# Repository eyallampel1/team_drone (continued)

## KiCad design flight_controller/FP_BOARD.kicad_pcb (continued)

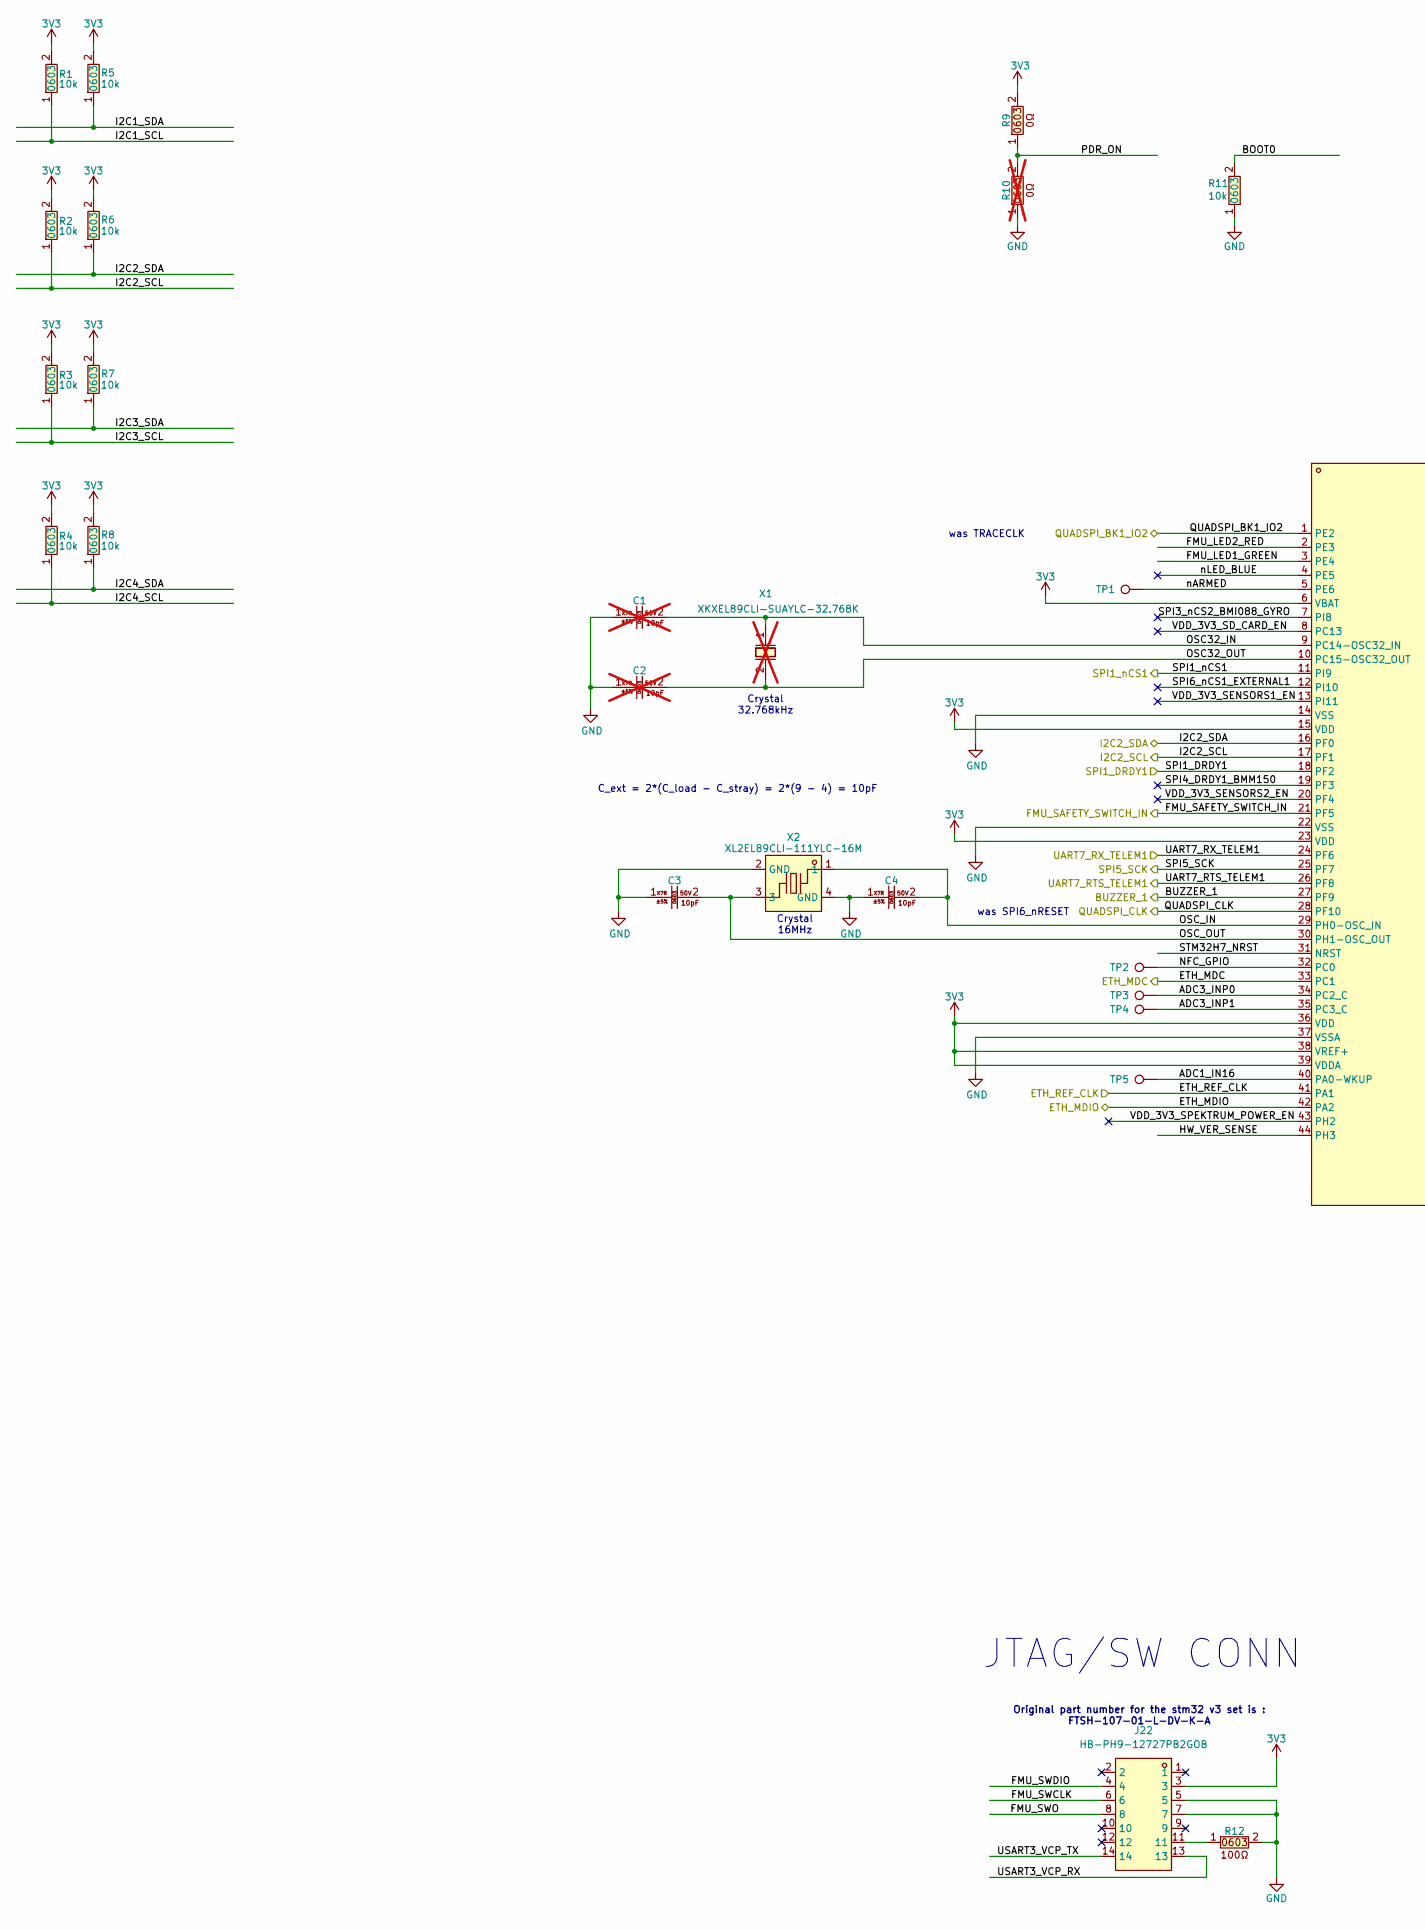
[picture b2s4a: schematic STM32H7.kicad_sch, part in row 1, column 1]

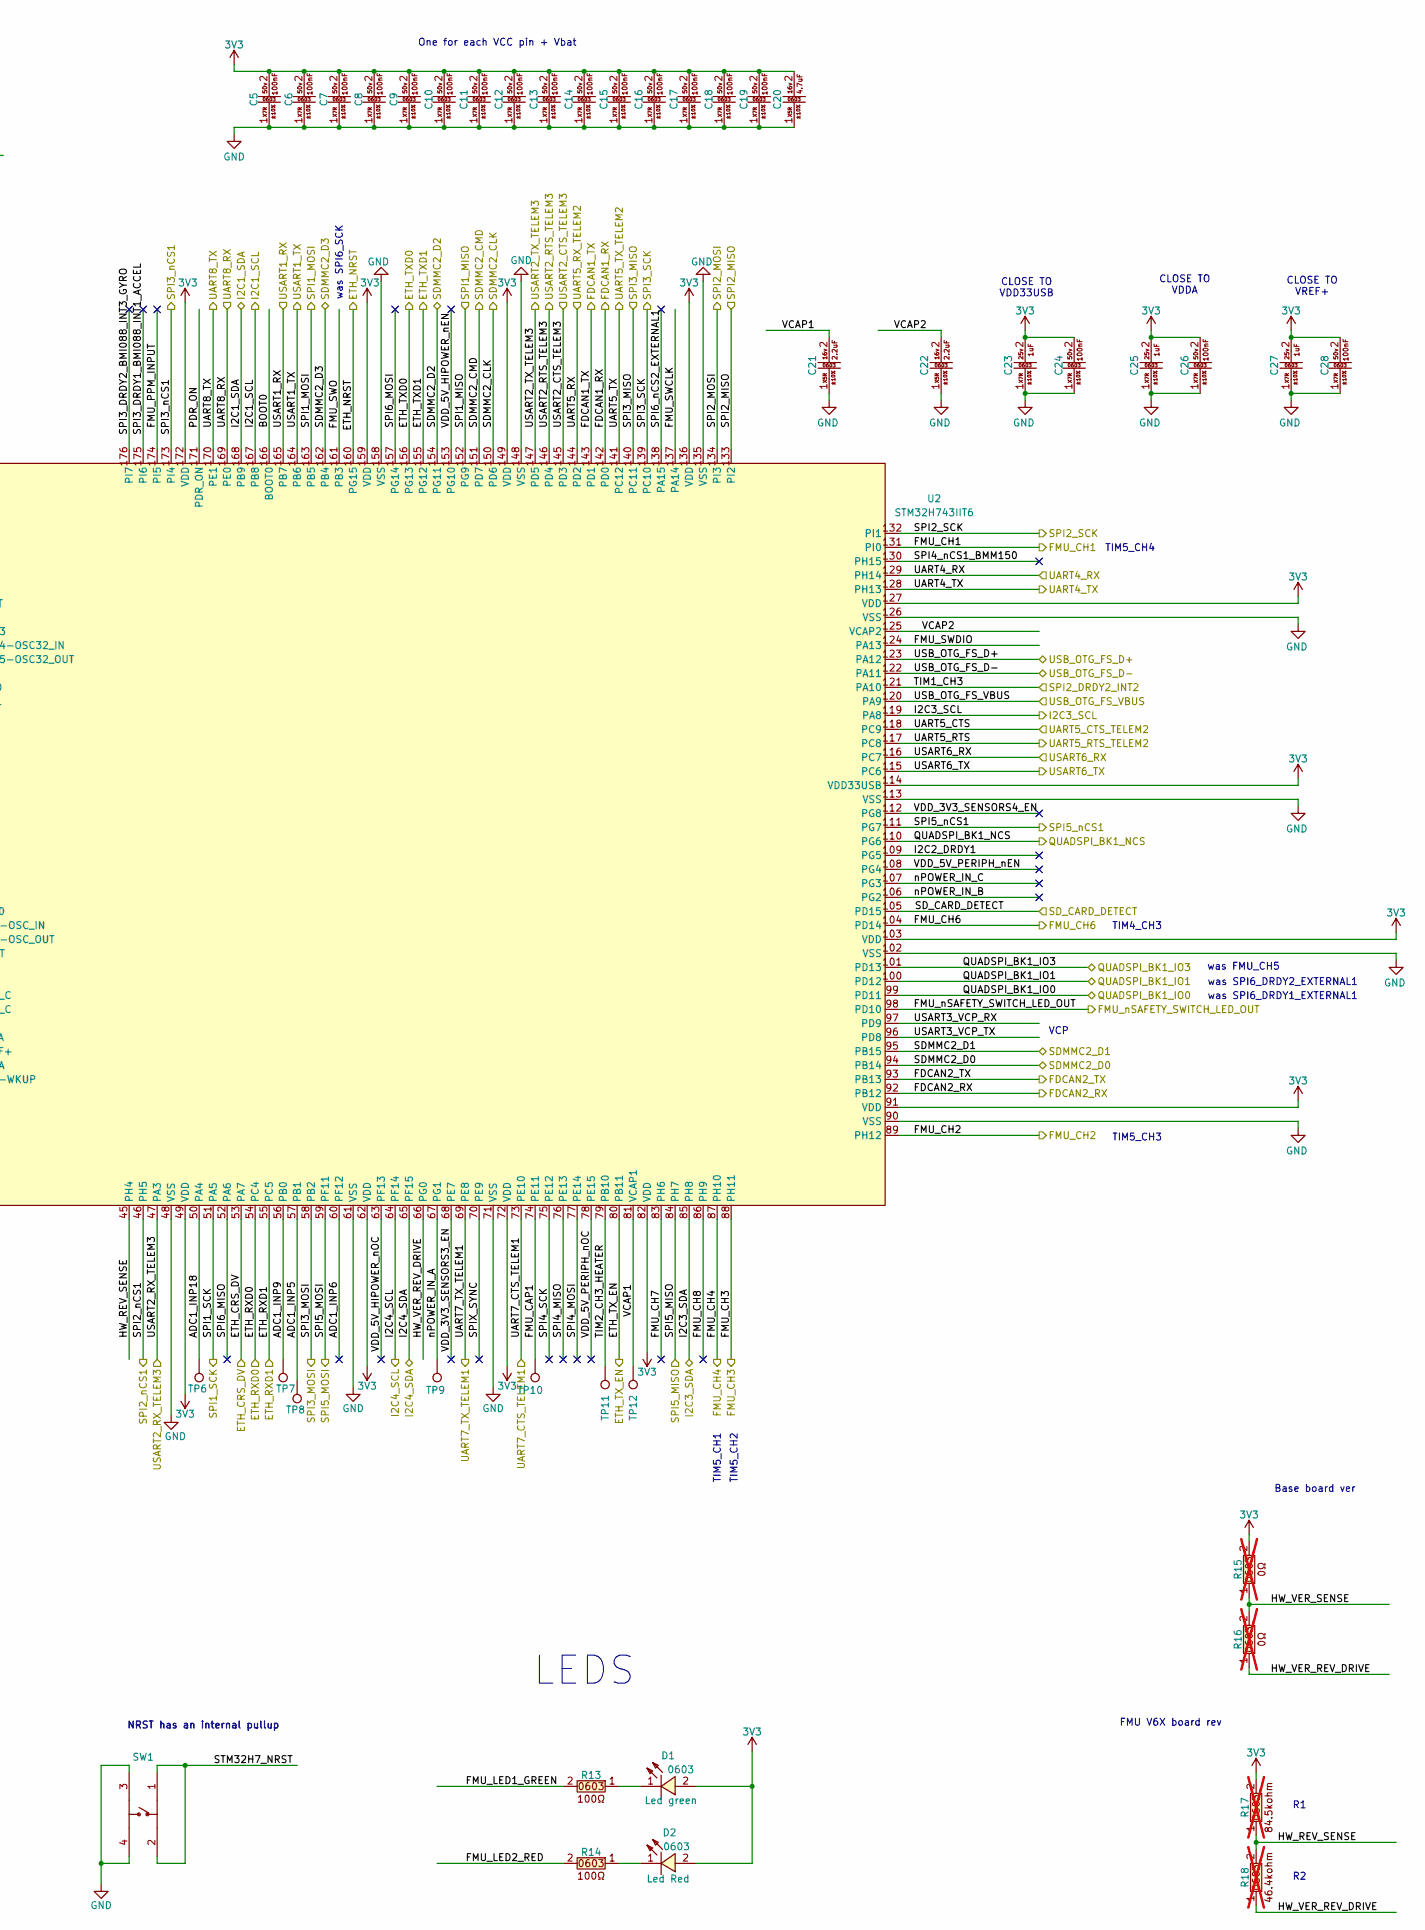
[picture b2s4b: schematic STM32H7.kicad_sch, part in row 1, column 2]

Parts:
C1, C2: CC0603JRNPO9BN100 (10pF , 0603 ,50V ,X7R); C0603; LCSC Part C106245; not fitted
C3, C4: CC0603JRNPO9BN100 (10pF , 0603 ,50V ,X7R); C0603; LCSC Part C106245
C5, C6, C7, C8, C9, C10, C11, C12, C13, C14, C15, C16, C17, C18, C19, C24, C26, C28: CC0603KRX7R9BB104 (100nf , 0603 ,50v ,X7R); C0603; LCSC Part C14663
C20: CL10A475KO8NNNC (4.7uf , 0603 ,16v ,X5R); C0603; LCSC Part C19666
C21, C22: CL10A225KO8NNNC (2.2uf , 0603,16v,X5R); C0603; LCSC Part C23630
C23, C25, C27: CL10B105KA8NNNC (1uf ,0603 ,25v ,X7R); C0603; LCSC Part C29936
D1: 0603 Green 509-620mcd; LED0603-RD; LCSC Part C12624
D2: KT-0603R; LED0603-RD; LCSC Part C2286
J22: HB-PH9-12727PB2GOB; HDR-SMD_14P-P1.27-V-M-R2-C7-LS5.5; LCSC Part C6332251
R1, R2, R3, R4, R5, R6, R7, R8, R11: 0603WAF1002T5E; R0603; LCSC Part C25804
R9: 603WAF0000T5E (0ohm , 0603); R0603; LCSC Part C21189
R10, R15, R16: 603WAF0000T5E (0ohm , 0603); R0603; LCSC Part C21189; not fitted
R12, R13, R14: 603WAF1000T5E (100ohm , 0603); R0603; LCSC Part C22775
R17: 0603WAF8452T5E (84.5kohm , 0603); R0603; LCSC Part C23118; not fitted
R18: FRC0603F4642TS (46.4kohm , 0603); R0603; LCSC Part C3013203; not fitted
SW1: 6.0*6.0*6.0; SW-SMD_4P-L6.0-W6.0-P4.50-LS8.6; LCSC Part C5127964
TP1, TP2, TP3, TP4, TP5, TP6, TP7, TP8, TP9, TP10, TP11, TP12: TestPoint; TestPoint_Pad_2.0x2.0mm
U2: STM32H743IIT6; LQFP-176_L24.0-W24.0-P0.50-LS26.0-BL; LCSC Part C89597
X1: XKXEL89CLI-SUAYLC-32.768K; OSC-SMD_2P-L3.2-W1.5; LCSC Part C17179430; not fitted
X2: XL2EL89CLI-111YLC-16M; CRYSTAL-SMD_4P-L3.2-W2.5-BL; LCSC Part C5444547

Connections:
/BUZZER_1: U2.27 (PF9); also elsewhere on the board
/ETH_CRS_DV: U2.53 (PA7); also elsewhere on the board
/ETH_MDC: U2.33 (PC1); also elsewhere on the board
/ETH_MDIO: U2.42 (PA2); also elsewhere on the board
/ETH_NRST: U2.160 (PG15); also elsewhere on the board
/ETH_REF_CLK: U2.41 (PA1); also elsewhere on the board
/ETH_RXD0: U2.54 (PC4); also elsewhere on the board
/ETH_RXD1: U2.55 (PC5); also elsewhere on the board
/ETH_TXD0: U2.156 (PG13); also elsewhere on the board
/ETH_TXD1: U2.155 (PG12); also elsewhere on the board
/ETH_TX_EN: U2.80 (PB11); also elsewhere on the board
/FDCAN1_RX: U2.142 (PD0); also elsewhere on the board
/FDCAN1_TX: U2.143 (PD1); also elsewhere on the board
/FDCAN2_RX: U2.92 (PB12); also elsewhere on the board
/FDCAN2_TX: U2.93 (PB13); also elsewhere on the board
/FMU_CH1: U2.131 (PI0); also elsewhere on the board
/FMU_CH2: U2.89 (PH12); also elsewhere on the board
/FMU_CH3: U2.88 (PH11); also elsewhere on the board
/FMU_CH4: U2.87 (PH10); also elsewhere on the board
/FMU_CH6: U2.104 (PD14); also elsewhere on the board
/FMU_SAFETY_SWITCH_IN: U2.21 (PF5); also elsewhere on the board
/FMU_nSAFETY_SWITCH_LED_OUT: U2.98 (PD10); also elsewhere on the board
/I2C1_SCL: R1.1, U2.167 (PB8); also elsewhere on the board
/I2C1_SDA: R5.1, U2.168 (PB9); also elsewhere on the board
/I2C2_SCL: R2.1, U2.17 (PF1); also elsewhere on the board
/I2C2_SDA: R6.1, U2.16 (PF0); also elsewhere on the board
/I2C3_SCL: R3.1, U2.119 (PA8); also elsewhere on the board
/I2C3_SDA: R7.1, U2.85 (PH8); also elsewhere on the board
/I2C4_SCL: R4.1, U2.64 (PF14); also elsewhere on the board
/I2C4_SDA: R8.1, U2.65 (PF15); also elsewhere on the board
/QUADSPI_BK1_IO0: U2.99 (PD11); also elsewhere on the board
/QUADSPI_BK1_IO1: U2.100 (PD12); also elsewhere on the board
/QUADSPI_BK1_IO2: U2.1 (PE2); also elsewhere on the board
/QUADSPI_BK1_IO3: U2.101 (PD13); also elsewhere on the board
/QUADSPI_BK1_NCS: U2.110 (PG6); also elsewhere on the board
/QUADSPI_CLK: U2.28 (PF10); also elsewhere on the board
/SDMMC2_CLK: U2.150 (PD6); also elsewhere on the board
/SDMMC2_CMD: U2.151 (PD7); also elsewhere on the board
/SDMMC2_D0: U2.94 (PB14); also elsewhere on the board
/SDMMC2_D1: U2.95 (PB15); also elsewhere on the board
/SDMMC2_D2: U2.154 (PG11); also elsewhere on the board
/SDMMC2_D3: U2.162 (PB4); also elsewhere on the board
/SD_CARD_DETECT: U2.105 (PD15); also elsewhere on the board
/SPI1_DRDY1: U2.18 (PF2); also elsewhere on the board
/SPI1_MISO: U2.152 (PG9); also elsewhere on the board
/SPI1_MOSI: U2.163 (PB5); also elsewhere on the board
/SPI1_SCK: U2.51 (PA5); also elsewhere on the board
/SPI1_nCS1: U2.11 (PI9); also elsewhere on the board
/SPI2_DRDY2_INT2: U2.121 (PA10); also elsewhere on the board
/SPI2_MISO: U2.133 (PI2); also elsewhere on the board
/SPI2_MOSI: U2.134 (PI3); also elsewhere on the board
/SPI2_SCK: U2.132 (PI1); also elsewhere on the board
/SPI2_nCS1: U2.46 (PH5); also elsewhere on the board
/SPI3_MISO: U2.140 (PC11); also elsewhere on the board
/SPI3_MOSI: U2.58 (PB2); also elsewhere on the board
/SPI3_SCK: U2.139 (PC10); also elsewhere on the board
/SPI3_nCS1: U2.173 (PI4); also elsewhere on the board
/SPI5_MISO: U2.84 (PH7); also elsewhere on the board
/SPI5_MOSI: U2.59 (PF11); also elsewhere on the board
/SPI5_SCK: U2.25 (PF7); also elsewhere on the board
/SPI5_nCS1: U2.111 (PG7); also elsewhere on the board
/STM32F1/USART6_RX_FROM_IO-RC_INPUT: U2.116 (PC7); also elsewhere on the board
/STM32F1/USART6_TX_TO_IO-NC: U2.115 (PC6); also elsewhere on the board
/STM32H7/ADC1_IN16: TP5.1, U2.40 (PA0-WKUP)
/STM32H7/ADC1_INP5: TP8.1, U2.57 (PB1)
/STM32H7/ADC1_INP6: U2.60 (PF12)
/STM32H7/ADC1_INP9: TP7.1, U2.56 (PB0)
/STM32H7/ADC1_INP18: TP6.1, U2.50 (PA4)
/STM32H7/ADC3_INP0: TP3.1, U2.34 (PC2_C)
/STM32H7/ADC3_INP1: TP4.1, U2.35 (PC3_C)
/STM32H7/BOOT0: R11.2, U2.166 (BOOT0)
/STM32H7/FMU_CAP1: TP10.1, U2.74 (PE11)
/STM32H7/FMU_CH7: U2.83 (PH6)
/STM32H7/FMU_CH8: U2.86 (PH9)
/STM32H7/FMU_LED1_GREEN: R13.2, U2.3 (PE4)
/STM32H7/FMU_LED2_RED: R14.2, U2.2 (PE3)
/STM32H7/FMU_PPM_INPUT: U2.174 (PI5)
/STM32H7/FMU_SWCLK: J22.6, U2.137 (PA14)
/STM32H7/FMU_SWDIO: J22.4, U2.124 (PA13)
/STM32H7/FMU_SWO: J22.8, U2.161 (PB3)
/STM32H7/HW_REV_SENSE: R17.1, R18.2, U2.45 (PH4)
/STM32H7/HW_VER_REV_DRIVE: R16.1, R18.1, U2.66 (PG0)
/STM32H7/HW_VER_SENSE: R15.1, R16.2, U2.44 (PH3)
/STM32H7/I2C2_DRDY1: U2.109 (PG5)
/STM32H7/NFC_GPIO: TP2.1, U2.32 (PC0)
/STM32H7/OSC32_IN: C1.2, U2.9 (PC14-OSC32_IN), X1.1
/STM32H7/OSC32_OUT: C2.2, U2.10 (PC15-OSC32_OUT), X1.2
/STM32H7/OSC_IN: C4.2, U2.29 (PH0-OSC_IN), X2.1
/STM32H7/OSC_OUT: C3.2, U2.30 (PH1-OSC_OUT), X2.3
/STM32H7/PDR_ON: R9.1, R10.2, U2.171 (PDR_ON)
/STM32H7/SPI3_DRDY1_BMI088_INT1_ACCEL: U2.175 (PI6)
/STM32H7/SPI3_DRDY2_BMI088_INT3_GYRO: U2.176 (PI7)
/STM32H7/SPI3_nCS2_BMI088_GYRO: U2.7 (PI8)
/STM32H7/SPI4_DRDY1_BMM150: U2.19 (PF3)
/STM32H7/SPI4_MISO: U2.76 (PE13)
/STM32H7/SPI4_MOSI: U2.77 (PE14)
/STM32H7/SPI4_SCK: U2.75 (PE12)
/STM32H7/SPI4_nCS1_BMM150: U2.130 (PH15)
/STM32H7/SPI6_MISO: U2.52 (PA6)
/STM32H7/SPI6_MOSI: U2.157 (PG14)
/STM32H7/SPI6_nCS1_EXTERNAL1: U2.12 (PI10)
/STM32H7/SPI6_nCS2_EXTERNAL1: U2.138 (PA15)
/STM32H7/SPIX_SYNC: U2.70 (PE9)
/STM32H7/STM32H7_NRST: SW1.1, SW1.2, U2.31 (NRST)
/STM32H7/TIM2_CH3_HEATER: TP11.1, U2.79 (PB10)
/STM32H7/USART3_VCP_RX: J22.13, U2.97 (PD9)
/STM32H7/USART3_VCP_TX: J22.14, U2.96 (PD8)
/STM32H7/VCAP1: C21.2, TP12.1, U2.81 (VCAP1)
/STM32H7/VCAP2: C22.2, U2.125 (VCAP2)
/STM32H7/VDD_3V3_SD_CARD_EN: U2.8 (PC13)
/STM32H7/VDD_3V3_SENSORS1_EN: U2.13 (PI11)
/STM32H7/VDD_3V3_SENSORS2_EN: U2.20 (PF4)
/STM32H7/VDD_3V3_SENSORS3_EN: U2.68 (PE7)
/STM32H7/VDD_3V3_SENSORS4_EN: U2.112 (PG8)
/STM32H7/VDD_3V3_SPEKTRUM_POWER_EN: U2.43 (PH2)
/STM32H7/VDD_5V_HIPOWER_nEN: U2.153 (PG10)
/STM32H7/VDD_5V_HIPOWER_nOC: U2.63 (PF13)
/STM32H7/VDD_5V_PERIPH_nEN: U2.108 (PG4)
/STM32H7/VDD_5V_PERIPH_nOC: U2.78 (PE15)
/STM32H7/nARMED: TP1.1, U2.5 (PE6)
/STM32H7/nLED_BLUE: U2.4 (PE5)
/STM32H7/nPOWER_IN_A: TP9.1, U2.67 (PG1)
/STM32H7/nPOWER_IN_B: U2.106 (PG2)
/STM32H7/nPOWER_IN_C: U2.107 (PG3)
/UART1_RX_GPS1: U2.165 (PB7); also elsewhere on the board
/UART1_TX_GPS1: U2.164 (PB6); also elsewhere on the board
/UART2_CTS_TELEM3: U2.145 (PD3); also elsewhere on the board
/UART2_RTS_TELEM3: U2.146 (PD4); also elsewhere on the board
/UART2_RX_TELEM3: U2.47 (PA3); also elsewhere on the board
/UART2_TX_TELEM3: U2.147 (PD5); also elsewhere on the board
/UART4_RX: U2.129 (PH14); also elsewhere on the board
/UART4_TX: U2.128 (PH13); also elsewhere on the board
/UART5_CTS_TELEM2: U2.118 (PC9); also elsewhere on the board
/UART5_RTS_TELEM2: U2.117 (PC8); also elsewhere on the board
/UART5_RX_TELEM2: U2.144 (PD2); also elsewhere on the board
/UART5_TX_TELEM2: U2.141 (PC12); also elsewhere on the board
/UART7_CTS_TELEM1: U2.73 (PE10); also elsewhere on the board
/UART7_RTS_TELEM1: U2.26 (PF8); also elsewhere on the board
/UART7_RX_TELEM1: U2.24 (PF6); also elsewhere on the board
/UART7_TX_TELEM1: U2.69 (PE8); also elsewhere on the board
/UART8_RX_GPS2: U2.169 (PE0); also elsewhere on the board
/UART8_TX_GPS2: U2.170 (PE1); also elsewhere on the board
/USB_OTG_FS_D+: U2.123 (PA12); also elsewhere on the board
/USB_OTG_FS_D-: U2.122 (PA11); also elsewhere on the board
/USB_OTG_FS_VBUS: U2.120 (PA9); also elsewhere on the board
unnamed: D1.1 (K), R13.1
unnamed: D2.1 (K), R14.1
unnamed: J22.11, R12.1

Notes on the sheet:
was SPI6_nRESET
Crystal 32.768kHz
was TRACECLK
C_ext = 2*(C_load - C_stray) = 2*(9 - 4) = 10pF
TIM4_CH3
CLOSE TO VDDA
CLOSE TO VREF+
LEDS
Original part number for the stm32 v3 set is : FTSH-107-01-L-DV-K-A
FMU V6X board rev
TIM5_CH1
NRST has an internal pullup
was FMU_CH5
Base board ver
Crystal 16MHz
TIM5_CH3
was SPI6_SCK
VCP
was SPI6_DRDY2_EXTERNAL1
TIM5_CH4
One for each VCC pin + Vbat
was SPI6_DRDY1_EXTERNAL1
JTAG/SW CONN
TIM5_CH2
CLOSE TO VDD33USB

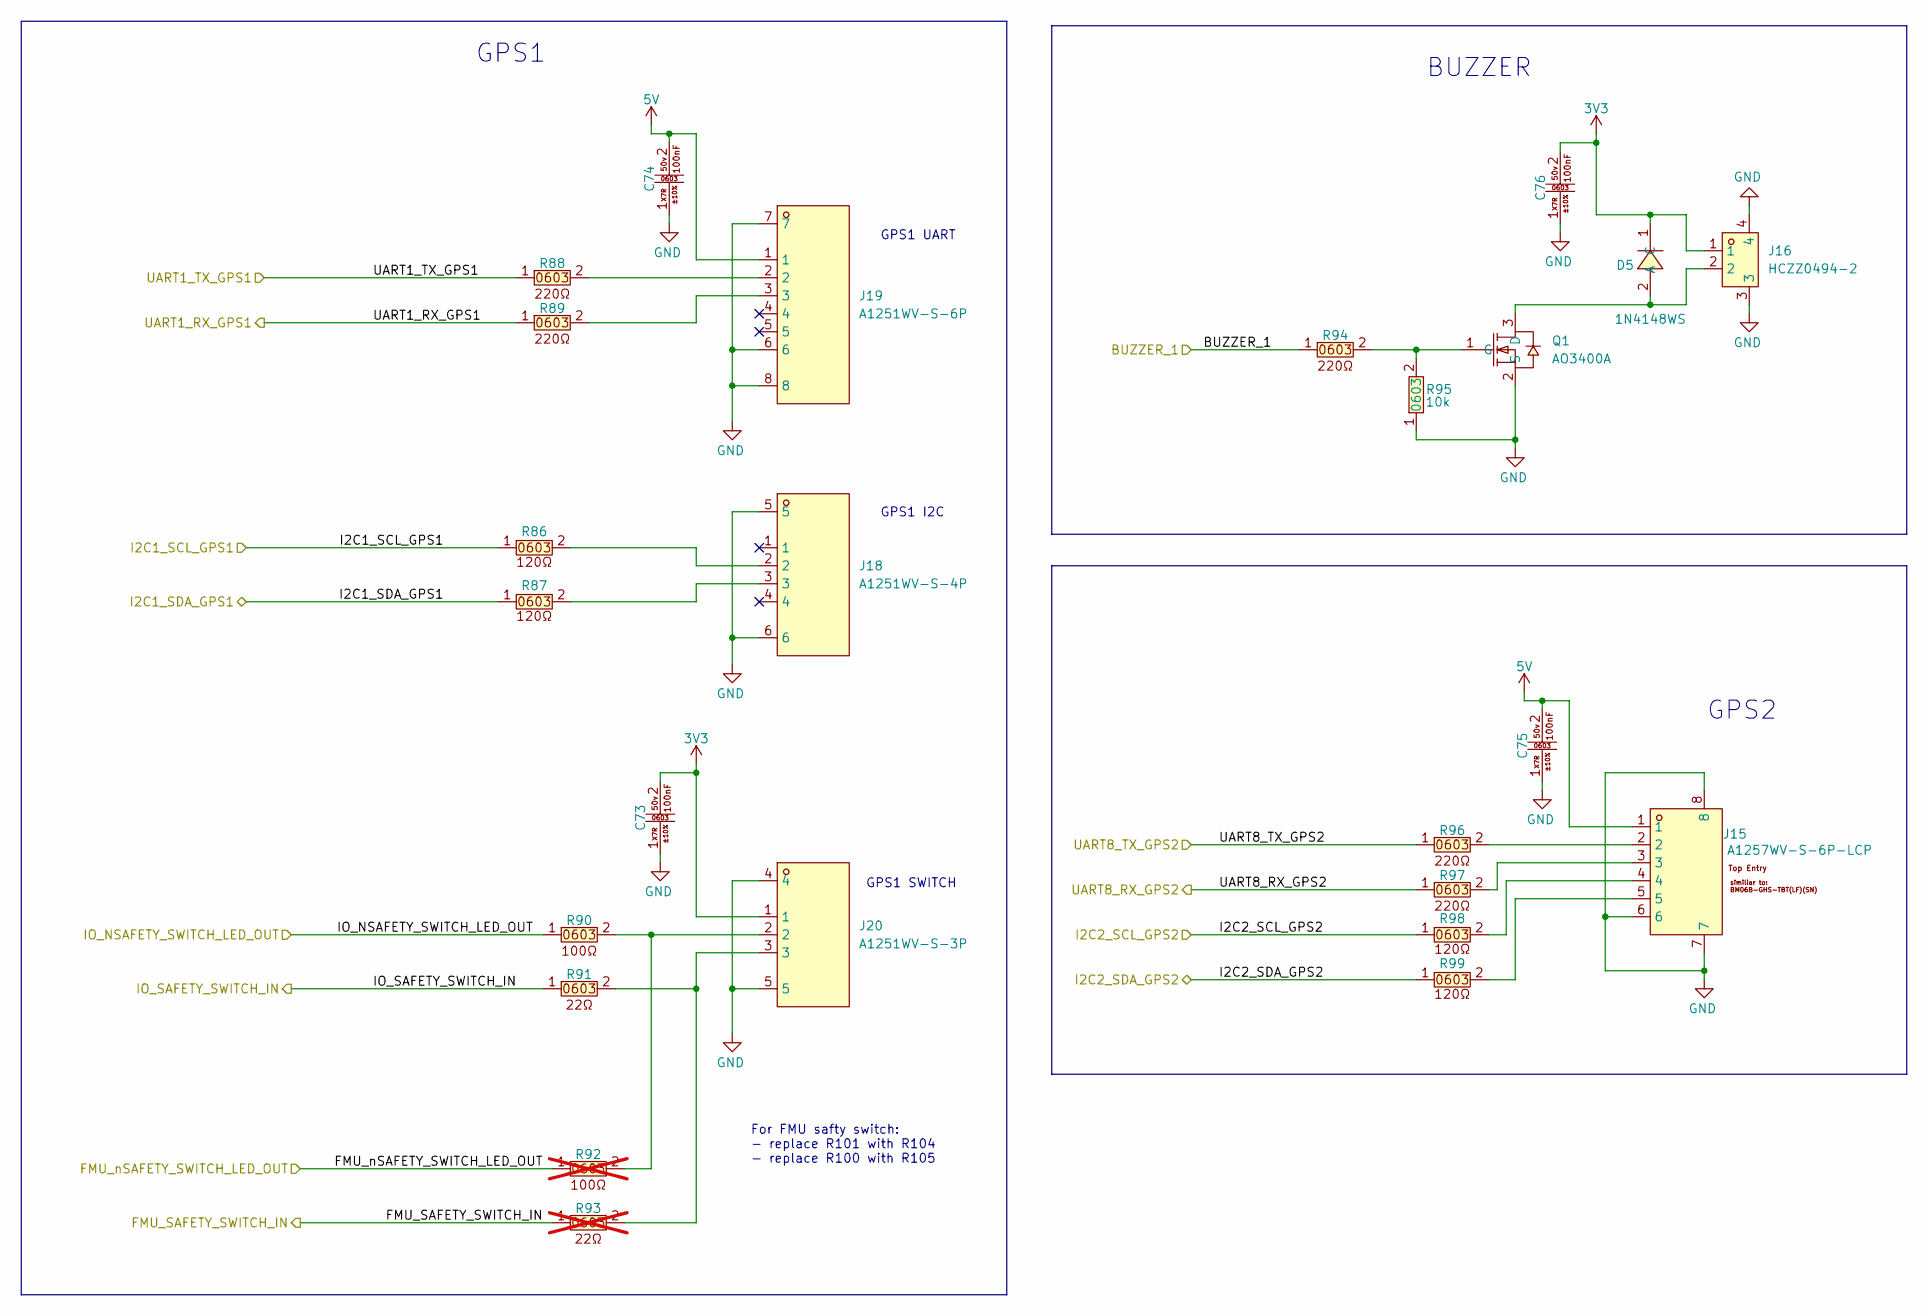
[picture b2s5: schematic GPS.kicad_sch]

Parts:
C73, C74, C75, C76: CC0603KRX7R9BB104 (100nf , 0603 ,50v ,X7R); C0603; LCSC Part C14663
D5: 1N4148WS; SOD-323_L1.8-W1.3-LS2.5-RD; LCSC Part C917117
J15: A1257WV-S-6P-LCP; CONN-SMD_A1257WV-S-6P; LCSC Part C225122
J16: HCZZ0494-2; CONN-SMD_HCZZ0494-2; LCSC Part C7433498
J18: A1251WV-S-4P; CONN-SMD_4P-P1.25_A1251WV-S-4P; LCSC Part C225106
J19: A1251WV-S-6P; CONN-SMD_6P-P1.25_A1251WV-S-6P; LCSC Part C225108
J20: A1251WV-S-3P; CONN-SMD_3P-P1.25_A1251WV-S-3P; LCSC Part C225105
Q1: AO3400A; SOT-23-3_L2.9-W1.3-P1.90-LS2.4-BR; LCSC Part C20917
R86, R87, R98, R99: 603WAF1200T5E; R0603; LCSC Part C22787
R88, R89, R94, R96, R97: 0603WAF2200T5E (220ohm , 0603); R0603; LCSC Part C22962
R90: 603WAF1000T5E (100ohm , 0603); R0603; LCSC Part C22775
R91: 603WAF220JT5E (22ohm , 0603); R0603; LCSC Part C23345
R92: 603WAF1000T5E (100ohm , 0603); R0603; LCSC Part C22775; not fitted
R93: 603WAF220JT5E (22ohm , 0603); R0603; LCSC Part C23345; not fitted
R95: 0603WAF1002T5E; R0603; LCSC Part C25804

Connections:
/BUZZER_1: R94.1; also elsewhere on the board
/FMU_SAFETY_SWITCH_IN: R93.1; also elsewhere on the board
/FMU_nSAFETY_SWITCH_LED_OUT: R92.1; also elsewhere on the board
/I2C1_SCL: R86.1; also elsewhere on the board
/I2C1_SDA: R87.1; also elsewhere on the board
/I2C2_SCL: R98.1; also elsewhere on the board
/I2C2_SDA: R99.1; also elsewhere on the board
/IO_NSAFETY_SWITCH_LED_OUT: R90.1; also elsewhere on the board
/IO_SAFETY_SWITCH_IN: R91.1; also elsewhere on the board
/UART1_RX_GPS1: R89.1; also elsewhere on the board
/UART1_TX_GPS1: R88.1; also elsewhere on the board
/UART8_RX_GPS2: R97.1; also elsewhere on the board
/UART8_TX_GPS2: R96.1; also elsewhere on the board
unnamed: D5.2 (A), J16.2, Q1.3 (D)
unnamed: J18.2, R86.2
unnamed: J18.3, R87.2
unnamed: J19.2, R88.2
unnamed: J19.3, R89.2
unnamed: J20.2, R90.2, R92.2
unnamed: J20.3, R91.2, R93.2
unnamed: Q1.1 (G), R94.2, R95.2

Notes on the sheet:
For FMU safty switch: - replace R101 with R104 - replace R100 with R105
GPS1
BUZZER
GPS2
GPS1 UART
GPS1 I2C
GPS1 SWITCH

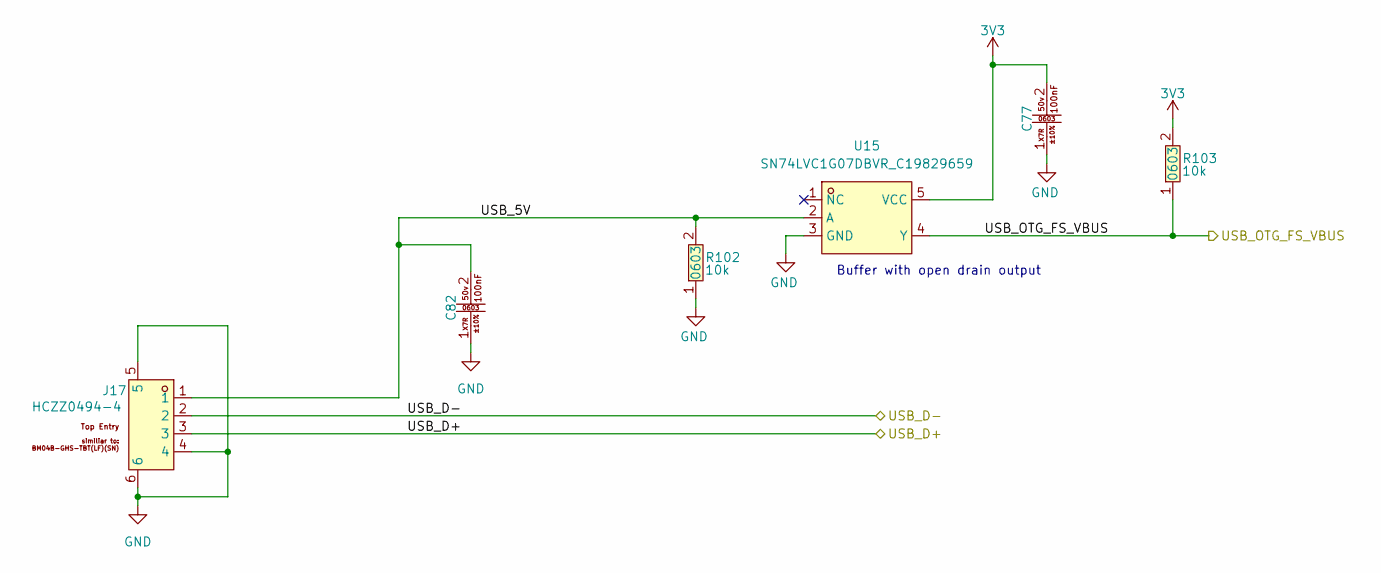
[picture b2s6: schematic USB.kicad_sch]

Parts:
C77, C82: CC0603KRX7R9BB104 (100nf , 0603 ,50v ,X7R); C0603; LCSC Part C14663
J17: HCZZ0494-4; CONN-SMD_4P-P1.25_BM04B-GHS-TBT-LF-SN; LCSC Part C7433500
R102, R103: 0603WAF1002T5E; R0603; LCSC Part C25804
U15: SN74LVC1G07DBVR_C19829659; SOT-23-5_L3.0-W1.5-P0.95-LS2.8-BL; LCSC Part C19829659

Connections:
/USB/USB_5V: C82.2, J17.1, R102.2, U15.2 (A)
/USB_OTG_FS_D+: J17.3; also elsewhere on the board
/USB_OTG_FS_D-: J17.2; also elsewhere on the board
/USB_OTG_FS_VBUS: R103.1, U15.4 (Y); also elsewhere on the board

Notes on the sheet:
Buffer with open drain output

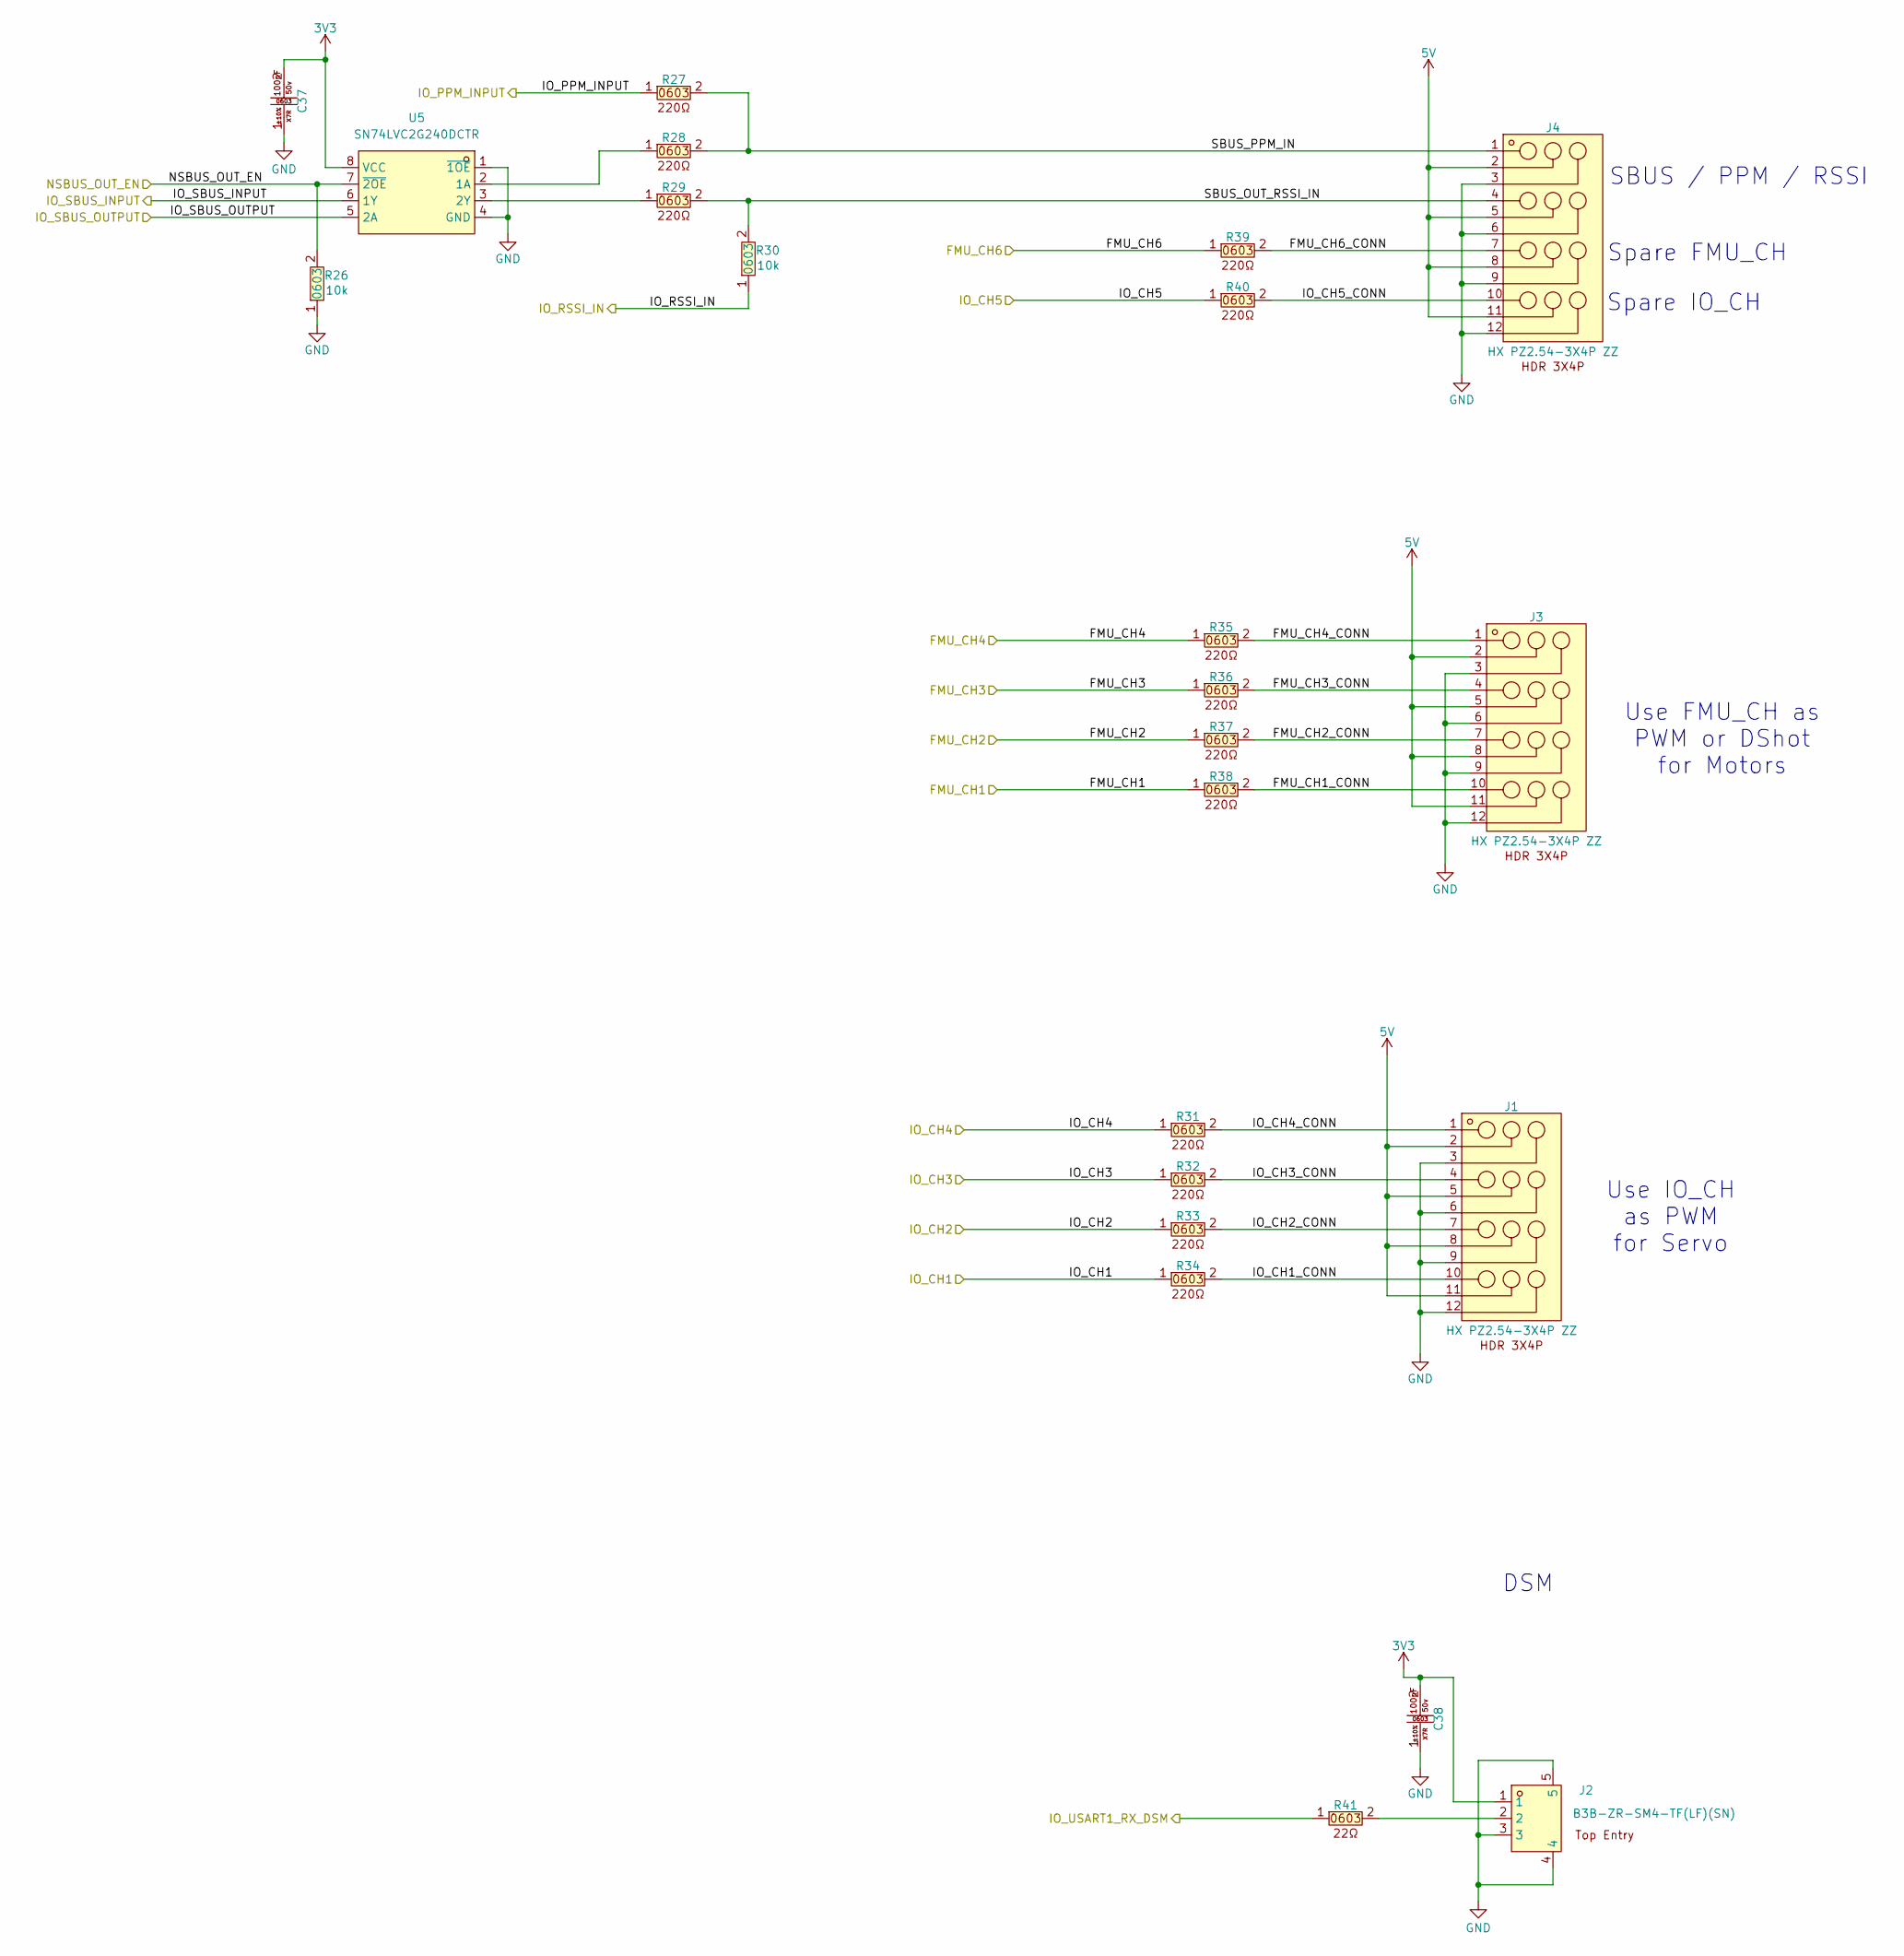
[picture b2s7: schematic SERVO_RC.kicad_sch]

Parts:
C37, C38: CC0603KRX7R9BB104 (100nf , 0603 ,50v ,X7R); C0603; LCSC Part C14663
J1, J3, J4: HX PZ2.54-3X4P ZZ; HDR-TH_12P-P2.54-V-M-R3-C4-S2.54; LCSC Part C32713291
J2: B3B-ZR-SM4-TF(LF)(SN); CONN-SMD_B3B-ZR-SM4-TF; LCSC Part C489717
R26, R30: 0603WAF1002T5E; R0603; LCSC Part C25804
R27, R28, R29, R31, R32, R33, R34, R35, R36, R37, R38, R39, R40: 0603WAF2200T5E (220ohm , 0603); R0603; LCSC Part C22962
R41: 603WAF220JT5E (22ohm , 0603); R0603; LCSC Part C23345
U5: SN74LVC2G240DCTR; SM8_L3.0-W2.8-P0.65-LS4.0-BL; LCSC Part C2675797

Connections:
/FMU_CH1: R38.1; also elsewhere on the board
/FMU_CH2: R37.1; also elsewhere on the board
/FMU_CH3: R36.1; also elsewhere on the board
/FMU_CH4: R35.1; also elsewhere on the board
/FMU_CH6: R39.1; also elsewhere on the board
/IO_CH1: R34.1; also elsewhere on the board
/IO_CH2: R33.1; also elsewhere on the board
/IO_CH3: R32.1; also elsewhere on the board
/IO_CH4: R31.1; also elsewhere on the board
/IO_CH5: R40.1; also elsewhere on the board
/IO_PPM_INPUT: R27.1; also elsewhere on the board
/IO_RSSI_IN: R30.1; also elsewhere on the board
/IO_SBUS_INPUT: U5.6 (1Y); also elsewhere on the board
/IO_SBUS_OUTPUT: U5.5 (2A); also elsewhere on the board
/IO_USART1_RX_DSM: R41.1; also elsewhere on the board
/NSBUS_OUT_EN: R26.2, U5.7 (~2OE); also elsewhere on the board
/SERVO_RC/FMU_CH1_CONN: J3.10, R38.2
/SERVO_RC/FMU_CH2_CONN: J3.7, R37.2
/SERVO_RC/FMU_CH3_CONN: J3.4, R36.2
/SERVO_RC/FMU_CH4_CONN: J3.1, R35.2
/SERVO_RC/FMU_CH6_CONN: J4.7, R39.2
/SERVO_RC/IO_CH1_CONN: J1.10, R34.2
/SERVO_RC/IO_CH2_CONN: J1.7, R33.2
/SERVO_RC/IO_CH3_CONN: J1.4, R32.2
/SERVO_RC/IO_CH4_CONN: J1.1, R31.2
/SERVO_RC/IO_CH5_CONN: J4.10, R40.2
/SERVO_RC/SBUS_OUT_RSSI_IN: J4.4, R29.2, R30.2
/SERVO_RC/SBUS_PPM_IN: J4.1, R27.2, R28.2
unnamed: J2.2, R41.2
unnamed: R28.1, U5.2 (1A)
unnamed: R29.1, U5.3 (2Y)

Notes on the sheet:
Use IO_CH as PWM for Servo
Spare FMU_CH
Use FMU_CH as PWM or DShot for Motors
SBUS / PPM / RSSI
DSM
Spare IO_CH
